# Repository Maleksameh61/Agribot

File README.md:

# The AgriBot rover

> **Stardance reviewers:** the part I'm submitting is the PCB, which is everything in `PCB/` and `production/`. I started AgriBot before I'd even heard of Hack Club, so the chassis, motors and the rest were already underway. They're here so you can see what the board plugs into, but please review the board on its own.

AgriBot tops out at 1.4 km/h, so you can outwalk it, and that's fine, because its job is to drive to a GPS point, stop, push a soil probe into the ground and read moisture, temperature, pH, salinity (EC) and NPK, then go do it again somewhere else.

This repo is the board that runs all of that: three ESP32s, five buck converters, the motor driver links, the stepper for the probe, GPS, a SIM800L and two speakers, on 260 x 150 mm of 2 oz copper.

## How it works

The idea is that nobody drives it most of the time. You give it a list of GPS points and it goes to each one, with two HC-SR04s up front so it doesn't drive into a tree. When it gets there it stops, and a NEMA 17 on a rack and pinion pushes the RS485 soil probe down. Sensors reads the probe and saves the numbers with the GPS position. While it's parked the ESP32-CAM can look at the crops, and if it's too far out for WiFi, the Audio ESP32 texts me through the SIM800L.

You can also drive it from your phone, mostly to get it to the field or out of a ditch. The phone joins the WiFi that Sensors puts up and sends throttle and steering about 20 times a second. Sensors passes that down a UART to Motion, and Motion turns it into left and right speeds for the two Cytron MDD10A drivers. Video goes straight from the ESP32-CAM to your phone over the same WiFi, and two servos aim the camera.

Motion only moves while Sensors keeps talking to it. If 150 ms go by without a command, the motors stop, and that's the entire safety system. Yes, I thought about a real e-stop. At walking pace you can just catch it, and pulling an XT60 kills everything.

Sensors also reads temperature, humidity, pressure, light and an MPU6050, and shows what's going on on a 2.8" Cheap Yellow Display over a 4-pin cable. Audio plays sounds off a microSD through two speakers.

## Why I made it

Salty soil is the big problem on small farms in Egypt, and checking a field means walking it with a probe or sending samples to a lab. I wanted a rover to do the walking. I also wanted every part to come from shops in Cairo. The board and everything that plugs into it, with the JLC order and shipping, comes to about $167. The whole rover is more like $560, and most of that is the four gearmotors (1,200 EGP each at Makers) and the soil probe (3,750 EGP). I didn't see that coming when I picked them.

I took AgriBot to RobotChallenge in Beijing this August and came 4th in FreeStyle Senior. After that I redid the electronics. The plan was three separate boards (Motion, Sensors, Audio) talking over ESP-NOW, and I didn't like the chip that drives the motors depending on radio, so now it's one board with the three ESP32s wired together over UART and Sensors in the middle. Before you ask why there are still three: I counted about 39 GPIOs for everything on here, and a DevKit gives you about 24 you can actually use.

## Pictures

These are renders of the real board file. The boards aren't ordered yet, so no photos.

### PCB layout
Red is top copper, blue is bottom. The big red areas are the 12 V pour and the bottom is almost all ground.

### Front and back

### The three ESP32s
Motion, Sensors and Audio, left to right. Sensors is the only one with its WiFi on.

### Schematic

Full-size PDF: [`production/schematic.pdf`](production/schematic.pdf)

### Wiring
Every cable that leaves the board. The numbers on the board map match the plug names underneath. Wire colours are only suggestions, so go by pin number (pin 1 is the marked end of each plug).

## What's on the board

**Power**
- 2x XT60 inputs, one per 12 V 12 Ah battery pack
- A 20 A fuse on each pack before they join, so a shorted pack can't get fed by the good one
- 2 screw terminals that send 12 V out to the motor drivers
- A 5 A fuse and an MBR4045CT Schottky in front of everything that isn't a motor
- 5x LM2596 buck modules: 5 V for each ESP32, 5 V just for the servos, and 4.0 V for the SIM800L. Every rail has its own LED so you can see when one dies
- Battery voltage sense on Motion and Sensors (100k/22k dividers)
- 12 V pour on top, ground pour on the bottom, 2 oz copper because up to 20 A comes through here

**Motion ESP32**
- Signal connectors for 2x Cytron MDD10A, which run four 5840-31ZY worm gearmotors
- DRV8825 for the NEMA 17 that lowers the soil probe
- 2 servo headers for the camera pan/tilt
- 2 HC-SR04 connectors, with dividers so the 5 V echo doesn't cook the ESP32

**Sensors ESP32**
- AHT20 + BMP280, BH1750 and MPU6050 on one I2C bus
- NEO-6M GPS
- MAX485 module for the RS485 soil probe, plus a 12 V terminal to power the probe
- Cable to the CYD touchscreen
- 8 spare pins on a header for whatever I forgot

**Audio ESP32**
- 2x MAX98357A amps on one shared I2S bus, gain picked with a jumper on each
- microSD
- SIM800L
- 8 more spare pins

## Stuff I'm not sure about yet

A lot of this board is educated guesses, and one guess already nearly went wrong. The first LM2596 footprint was mirrored, so 12 V would have gone straight into the output side of every buck. I only caught it when I swapped in real 3D models and the module didn't line up with its pads. The pads are now 4 mm squares that fit every clone I could find, but I still want to measure one.

- The probe is the part I'm least sure about. A NEMA 17 on a rack and pinion pushes maybe 20 to 50 N, and the rover can't push down harder than it weighs anyway. Soft or tilled soil should be fine. Dry, packed clay, I don't know yet.
- The 5 A fuse covers every buck plus the stepper. My estimate is around 4 A worst case from 12 V, and I haven't measured anything.

## If you build one

- Set every LM2596 to its voltage before it's connected to anything, then hot glue the trimmer. 12 V into a MAX98357A kills it instantly, and the SIM800L wants 4.0 V, not 5.
- Set the DRV8825 current limit before you plug the stepper in.
- Use ceramic 20 A fuses, not glass, and zip tie them down. The clips hold by friction and this thing shakes.
- The camera power terminal has ground on pin 1, the opposite of the other power terminals. It's marked − / + on the board, so look before you screw the wires in.
- Put some kapton tape under each buck module. They sit flat on the board and their bottom pins can scratch through the solder mask.

## AI declaration

Short version: the board is mine, and AI helped me check it.

I drew the schematic, picked every part, and did the placement and routing myself. I used AI kind of like a second pair of eyes. It helped me clear DRC errors and catch problems I missed, and it told me about parts I'd forgotten, mostly passives like decoupling caps, dividers and pull-ups. It also helped me plan which ESP32 pin goes where and what track width to use on the power paths. Some of the custom KiCad symbols and footprints were made by AI, and I checked those against the real modules before using them.

The firmware is where I needed AI the most. It's big, and there were errors I couldn't fix on my own, so AI helped write and debug parts of it, usually one small section at a time. I worked on it for weeks, but you'll only see one commit, because I pushed the wrong versions before and had to upload it all again. There are a lot of comments in the code. I know that can look like AI, but I put them there so you can follow what each part does.

## Files

- `production/` - what you send off to get one made: `gerbers.zip` (Gerbers + drill files), `schematic.pdf` and a copy of the firmware
- `production/printables/` - STEP files for the 3D-printed parts: the four motor mounts and the ESP32-CAM pan/tilt
- `PCB/` - KiCad 10 project (`agribot.kicad_sch`, `agribot.kicad_pcb`, `agribot.kicad_pro`, custom footprints, symbols and 3D models)
- `CAD/agribot-pcb.step` - STEP of the assembled board with every module on it. It's 54 MB, which the GitHub website won't take, so I pushed it with git instead. The module models are real ones (Espressif, KiCad library, Sector7GP, a SIM800L repo, openbikesensor, and the JLCEDA/EasyEDA Official Library for the fuses and the KF128 terminals), credits are in `PCB/libraries/3dmodels/CREDITS.md`
- `CAD/agribot-full-assembly.step` - the whole rover exported from my Fusion file (agribot v15): the plywood chassis with everything mounted on it, including the CYD. 32 MB, so this one went up with git too. Open it if you want to see how it all fits before cutting any wood
- `firmware/` - code for all 5 chips: the Motion, Sensors and Audio ESP32s, the CYD and the ESP32-CAM. How to flash and test it is in `firmware/README.md`
- `BOM.csv` - the bare board: everything on the PCB or plugged into it, from Makers Electronics, Micro Ohm and Free Electronics, with links, USD and EGP prices, shipping, and the JLC quote I got on Nov 3 ($68.80 for 5 boards in 2 oz copper). About $167. The drivers, motors, batteries, probe and chassis aren't in it, since they're not part of the board
- `BOM/AgriBot_Entire_Project_Cost.xlsx` - the whole rover, board plus everything else (motors, drivers, batteries, probe, CYD, camera, chassis, screws). The totals work themselves out, and if you change the EGP rate at the top all the USD numbers change with it

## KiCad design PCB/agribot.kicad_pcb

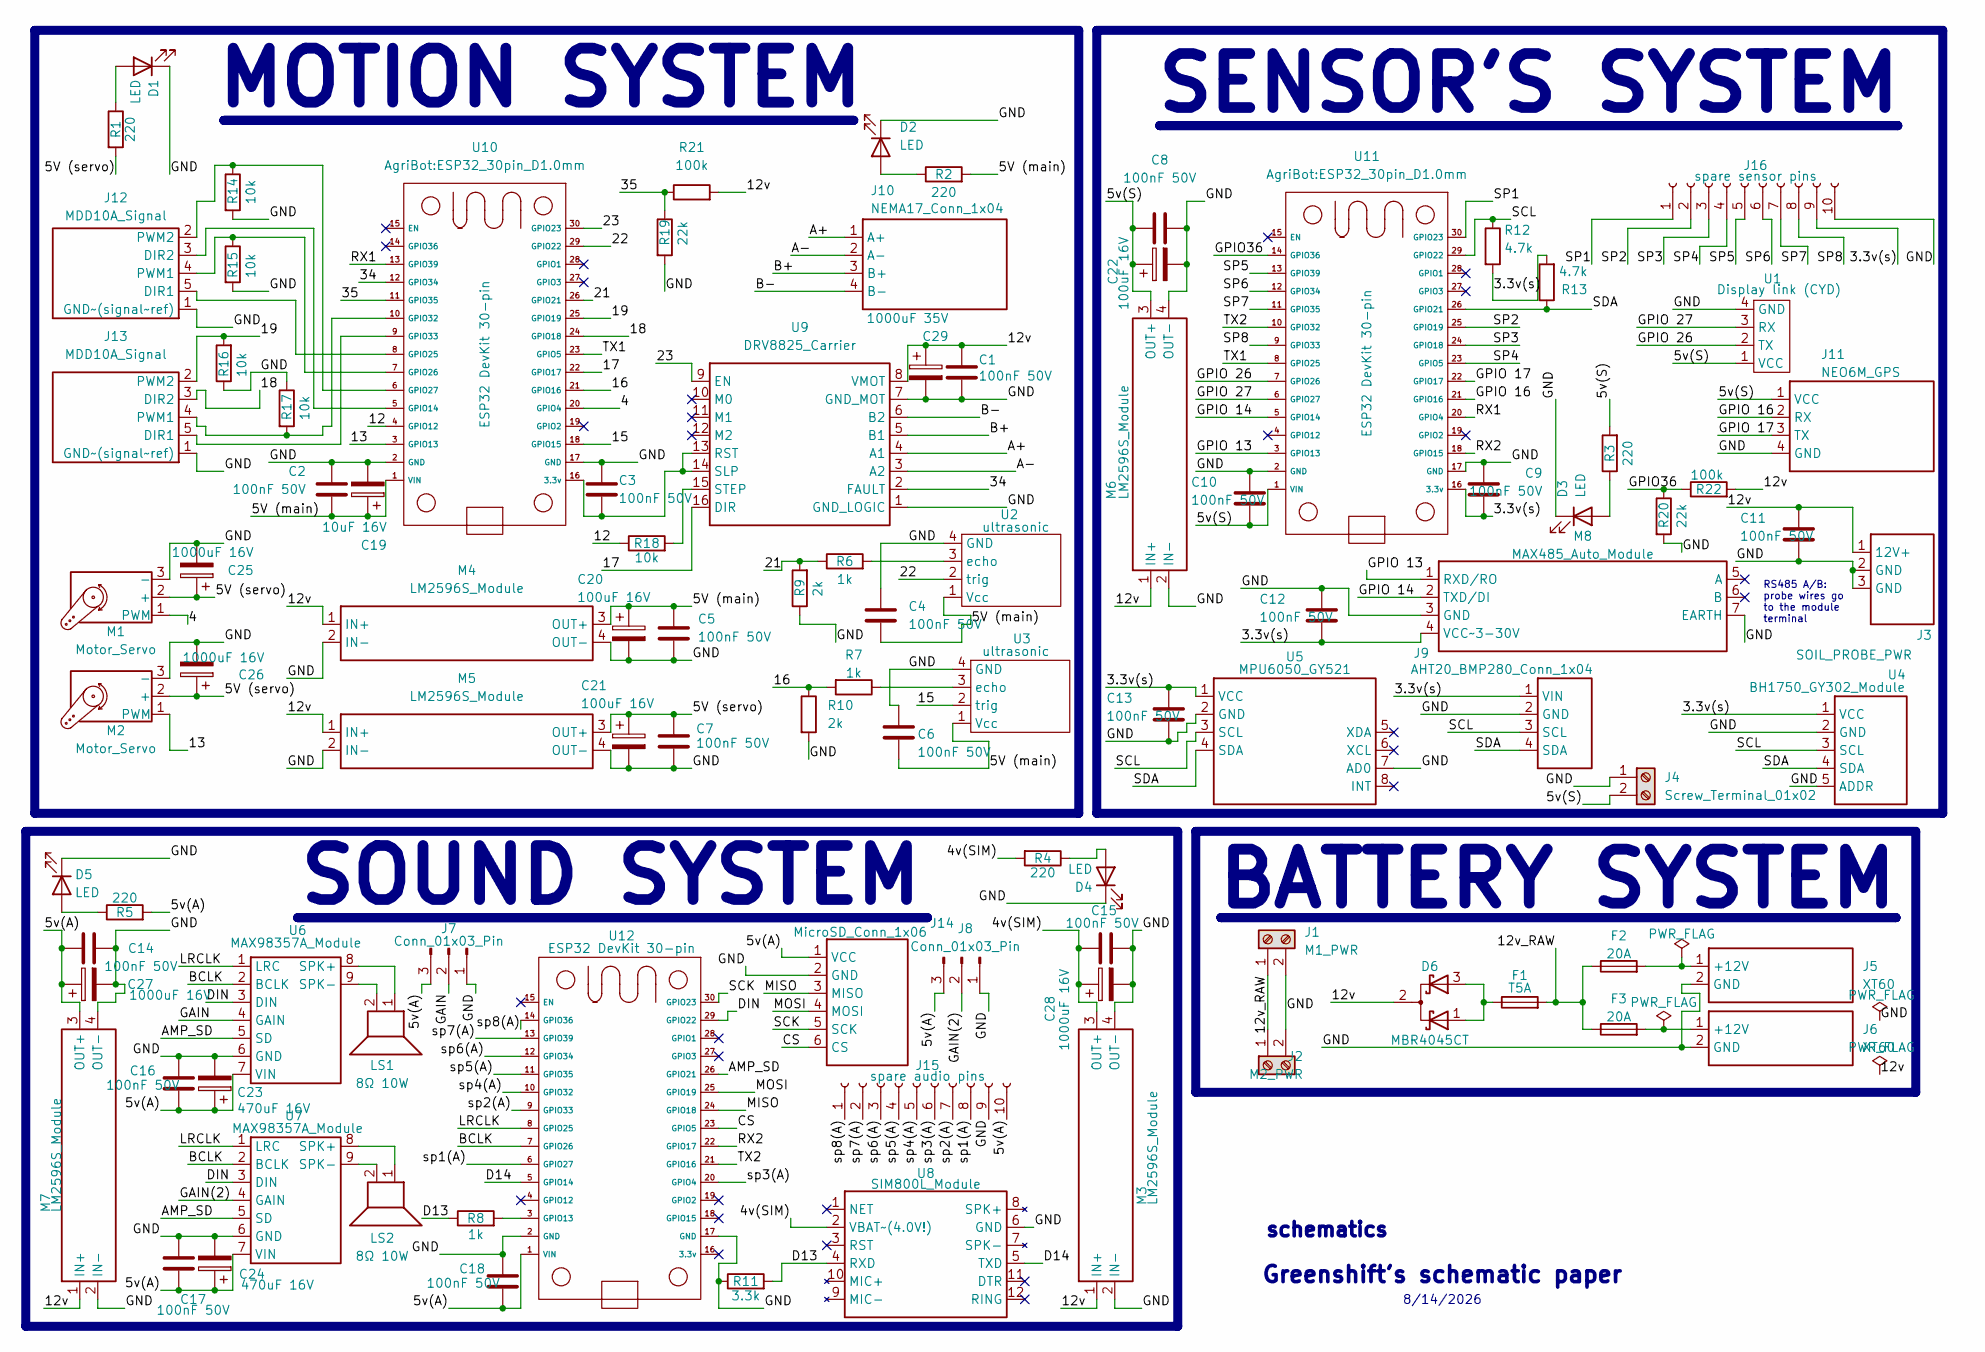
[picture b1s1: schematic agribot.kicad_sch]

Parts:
C1, C2, C3, C4, C5, C6, C7, C8, C9, C10, C11, C12, C13, C14, C15, C16, C17, C18: 100nF 50V; C_Disc_D5.0mm_W2.5mm_P5.00mm
C19: 10uF 16V; CP_Radial_D5.0mm_P2.00mm
C20, C21, C22: 100uF 16V; CP_Radial_D6.3mm_P2.50mm
C23, C24: 470uF 16V; CP_Radial_D10.0mm_P5.00mm
C25, C26, C27, C28: 1000uF 16V; CP_Radial_D10.0mm_P5.00mm
C29: 1000uF 35V; CP_Radial_D13.0mm_P5.00mm
D1, D2, D3, D4, D5: LED; LED_D5.0mm
D6: MBR4045CT; TO-220-3_Vertical
F1: T5A; Fuseholder_Clip-5x20mm_Littelfuse_111_Inline_P20.00x5.00mm_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
F2, F3: 20A; Fuseholder_Clip-5x20mm_Littelfuse_100_Inline_P20.50x4.60mm_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
J1: M1_PWR; KF128-7.5_1x02_P7.50mm_Horizontal
J2: M2_PWR; KF128-7.5_1x02_P7.50mm_Horizontal
J3: SOIL_PROBE_PWR; TerminalBlock_Phoenix_MKDS-1,5-3-5.08_1x03_P5.08mm_Horizont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
J4: Screw_Terminal_01x02; TerminalBlock_Phoenix_MKDS-1,5-2-5.08_1x02_P5.08mm_Horizont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
J5, J6: XT60; AMASS_XT60-M_1x02_P7.20mm_Vertical
J7, J8: Conn_01x03_Pin; PinHeader_1x03_P2.54mm_Vertical
J9: AHT20_BMP280_Conn_1x04; JST_XH_B4B-XH-A_1x04_P2.50mm_Vertical
J10: NEMA17_Conn_1x04; JST_XH_B4B-XH-A_1x04_P2.50mm_Vertical
J11: NEO6M_GPS; JST_XH_B4B-XH-A_1x04_P2.50mm_Vertical
J12, J13: MDD10A_Signal; JST_XH_B5B-XH-A_1x05_P2.50mm_Vertical
J14: MicroSD_Conn_1x06; PinSocket_1x06_P2.54mm_Vertical
J15: spare audio pins; PinSocket_2x05_P2.54mm_Vertical
J16: spare sensor pins; PinSocket_2x05_P2.54mm_Vertical
LS1, LS2: 8Ω 10W
M1, M2: Motor_Servo; PinHeader_1x03_P2.54mm_Vertical
M3, M4, M5, M6, M7: LM2596S_Module; LM2596S_Module_FlatMount_SMD
M8: MAX485_Auto_Module; JST_XH_B4B-XH-A_1x04_P2.50mm_Vertical
R1, R2, R3, R4, R5: 220; R_Axial_DIN0207_L6.3mm_D2.5mm_P10.16mm_Horizontal
R6, R7, R8: 1k; R_Axial_DIN0207_L6.3mm_D2.5mm_P10.16mm_Horizontal
R9, R10: 2k; R_Axial_DIN0207_L6.3mm_D2.5mm_P10.16mm_Horizontal
R11: 3.3k; R_Axial_DIN0207_L6.3mm_D2.5mm_P10.16mm_Horizontal
R12, R13: 4.7k; R_Axial_DIN0207_L6.3mm_D2.5mm_P10.16mm_Horizontal
R14, R15, R16, R17, R18: 10k; R_Axial_DIN0207_L6.3mm_D2.5mm_P10.16mm_Horizontal
R19, R20: 22k; R_Axial_DIN0207_L6.3mm_D2.5mm_P10.16mm_Horizontal
R21, R22: 100k; R_Axial_DIN0207_L6.3mm_D2.5mm_P10.16mm_Horizontal
U1: Display link (CYD); JST_XH_B4B-XH-A_1x04_P2.50mm_Vertical
U2, U3: ultrasonic; JST_XH_B4B-XH-A_1x04_P2.50mm_Vertical
U4: BH1750_GY302_Module; JST_XH_B5B-XH-A_1x05_P2.50mm_Vertical
U5: MPU6050_GY521; PinSocket_1x08_P2.54mm_Vertical
U6, U7: MAX98357A_Module; PinSocket_1x07_P2.54mm_Vertical
U8: SIM800L_Module
U9: DRV8825_Carrier; Pololu_Breakout-16_15.2x20.3mm_D1.0mm
U10, U11, U12: ESP32 DevKit 30-pin; ESP32_30pin_D1.0mm

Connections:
/3.3v(s): C9.2, C12.2, C13.1, J9.1 (VIN), J16.9, M8.4 (VCC~3-30V), R12.2, R13.2, U4.1 (VCC), U5.1 (VCC), U11.16 (3.3v)
/4: M1.1 (PWM), U10.20 (GPIO4)
/4v(SIM): C15.2, C28.1, M3.3 (OUT+), R4.2, U8.2 (VBAT~(4.0V!))
/5V (main): C2.2, C4.2, C5.1, C6.2, C19.1, C20.1, M4.3 (OUT+), R2.2, U2.1 (Vcc), U3.1 (Vcc), U10.1 (VIN)
/5V (servo): C7.1, C21.1, C25.1, C26.1, M1.2 (+), M2.2 (+), M5.3 (OUT+), R1.2
/5v(A): C14.2, C16.1, C17.1, C18.2, C23.1, C24.1, C27.1, J7.3, J8.3, J14.1 (VCC), J15.10, M7.3 (OUT+), R5.2, U6.7 (VIN), U7.7 (VIN), U12.1 (VIN)
/5v(S): C8.1, C10.2, C22.1, J4.2, J11.1 (VCC), M6.3 (OUT+), R3.2, U1.1 (VCC), U11.1 (VIN)
/12: R18.1, U10.4 (GPIO12)
/12v: C1.1, C11.1, C29.1, D6.2 (K), J3.1 (12V+), M3.1 (IN+), M4.1 (IN+), M5.1 (IN+), M6.1 (IN+), M7.1 (IN+), R21.2, R22.2, U9.8 (VMOT)
/12v_RAW: F1.2, F2.1, F3.1, J1.1, J2.1
/13: M2.1 (PWM), U10.3 (GPIO13)
/15: U3.2 (trig), U10.18 (GPIO15)
/16: R7.2, R10.1, U10.21 (GPIO16)
/17: U9.16 (DIR), U10.22 (GPIO17)
/18: J13.3 (DIR2), U10.24 (GPIO18)
/19: J13.2 (PWM2), R16.2, U10.25 (GPIO19)
/21: R6.1, R9.2, U10.26 (GPIO21)
/22: U2.2 (trig), U10.29 (GPIO22)
/23: U9.9 (EN), U10.30 (GPIO23)
/34: U9.2 (FAULT), U10.12 (GPIO34)
/35: R19.1, R21.1, U10.11 (GPIO35)
/A+: J10.1 (A+), U9.4 (A1)
/A-: J10.2 (A-), U9.3 (A2)
/AMP_SD: U6.5 (SD), U7.5 (SD), U12.26 (GPIO21)
/B+: J10.3 (B+), U9.5 (B1)
/B-: J10.4 (B-), U9.6 (B2)
/BCLK: U6.2 (BCLK), U7.2 (BCLK), U12.7 (GPIO26)
/CS: J14.6 (CS), U12.23 (GPIO5)
/D13: R8.1, R11.2, U8.4 (RXD)
/D14: U8.5 (TXD), U12.5 (GPIO14)
/DIN: U6.3 (DIN), U7.3 (DIN), U12.29 (GPIO22)
/GAIN: J7.2, U6.4 (GAIN)
/GAIN(2): J8.2, U7.4 (GAIN)
/GND: C1.2, C2.1, C3.1, C4.1, C5.2, C6.1, C7.2, C8.2, C9.1, C10.1, C11.2, C12.1, C13.2, C14.1, C15.1, C16.2, C17.2, C18.1, C19.2, C20.2, C21.2, C22.2, C23.2, C24.2, C25.2, C26.2, C27.2, C28.2, C29.2, D1.1 (K), D2.1 (K), D3.1 (K), D4.1 (K), D5.1 (K), J1.2, J2.2, J3.2 (GND), J3.3 (GND), J4.1, J5.2 (GND), J6.2 (GND), J7.1, J8.1, J9.2 (GND), J11.4 (GND), J12.1 (GND~(signal~ref)), J13.1 (GND~(signal~ref)), J14.2 (GND), J15.9, J16.10, M1.3 (-), M2.3 (-), M3.2 (IN-), M3.4 (OUT-), M4.2 (IN-), M4.4 (OUT-), M5.2 (IN-), M5.4 (OUT-), M6.2 (IN-), M6.4 (OUT-), M7.2 (IN-), M7.4 (OUT-), M8.3 (GND), M8.7 (EARTH), R9.1, R10.2, R11.1, R14.2, R15.2, R16.1, R17.1, R19.2, R20.2, U1.4 (GND), U2.4 (GND), U3.4 (GND), U4.2 (GND), U4.5 (ADDR), U5.2 (GND), U5.7 (AD0), U6.6 (GND), U7.6 (GND), U8.6 (GND), U9.1 (GND_LOGIC), U9.7 (GND_MOT), U10.2 (GND), U10.17 (GND), U11.2 (GND), U11.17 (GND), U12.2 (GND), U12.17 (GND)
/GPIO36: R20.1, R22.1, U11.14 (GPIO36)
/GPIO 13: M8.1 (RXD/RO), U11.3 (GPIO13)
/GPIO 14: M8.2 (TXD/DI), U11.5 (GPIO14)
/GPIO 16: J11.2 (RX), U11.21 (GPIO16)
/GPIO 17: J11.3 (TX), U11.22 (GPIO17)
/GPIO 26: U1.2 (TX), U11.7 (GPIO26)
/GPIO 27: U1.3 (RX), U11.6 (GPIO27)
/LRCLK: U6.1 (LRC), U7.1 (LRC), U12.8 (GPIO25)
/MISO: J14.3 (MISO), U12.24 (GPIO18)
/MOSI: J14.4 (MOSI), U12.25 (GPIO19)
/RX1: U10.13 (GPIO39), U11.20 (GPIO4)
/RX2: U11.18 (GPIO15), U12.22 (GPIO17)
/SCK: J14.5 (SCK), U12.30 (GPIO23)
/SCL: J9.3 (SCL), R12.1, U4.3 (SCL), U5.3 (SCL), U11.29 (GPIO22)
/SDA: J9.4 (SDA), R13.1, U4.4 (SDA), U5.4 (SDA), U11.26 (GPIO21)
/SP1: J16.1, U11.30 (GPIO23)
/SP2: J16.2, U11.25 (GPIO19)
/SP3: J16.3, U11.24 (GPIO18)
/SP4: J16.4, U11.23 (GPIO5)
/SP5: J16.5, U11.13 (GPIO39)
/SP6: J16.6, U11.12 (GPIO34)
/SP7: J16.7, U11.11 (GPIO35)
/SP8: J16.8, U11.9 (GPIO33)
/TX1: U10.23 (GPIO5), U11.8 (GPIO25)
/TX2: U11.10 (GPIO32), U12.21 (GPIO16)
/sp1(A): J15.8, U12.6 (GPIO27)
/sp2(A): J15.7, U12.9 (GPIO33)
/sp3(A): J15.6, U12.20 (GPIO4)
/sp4(A): J15.5, U12.10 (GPIO32)
/sp5(A): J15.4, U12.11 (GPIO35)
/sp6(A): J15.3, U12.12 (GPIO34)
/sp7(A): J15.2, U12.13 (GPIO39)
/sp8(A): J15.1, U12.14 (GPIO36)
unnamed: D1.2 (A), R1.1
unnamed: D2.2 (A), R2.1
unnamed: D3.2 (A), R3.1
unnamed: D4.2 (A), R4.1
unnamed: D5.2 (A), R5.1
unnamed: D6.1 (A), D6.3 (A), F1.1
unnamed: F2.2, J5.1 (+12V)
unnamed: F3.2, J6.1 (+12V)
unnamed: J12.5 (DIR1), U10.8 (GPIO25)
unnamed: J12.3 (DIR2), U10.5 (GPIO14)
unnamed: J12.4 (PWM1), R15.1, U10.7 (GPIO26)
unnamed: J12.2 (PWM2), R14.1, U10.6 (GPIO27)
unnamed: J13.5 (DIR1), U10.9 (GPIO33)
unnamed: J13.4 (PWM1), R17.2, U10.10 (GPIO32)
unnamed: LS1.1, U6.8 (SPK+)
unnamed: LS1.2, U6.9 (SPK-)
unnamed: LS2.1, U7.8 (SPK+)
unnamed: LS2.2, U7.9 (SPK-)
unnamed: R6.2, U2.3 (echo)
unnamed: R7.1, U3.3 (echo)
unnamed: R18.2, U9.15 (STEP)
unnamed: C3.2, U9.13 (RST), U9.14 (SLP), U10.16 (3.3v)
unnamed: R8.2, U12.3 (GPIO13)

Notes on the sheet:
BATTERY SYSTEM
Greenshift's schematic paper
schematics
SOUND SYSTEM
RS485 A/B: probe wires go to the module terminal
MOTION SYSTEM
8/14/2026
SENSOR'S SYSTEM

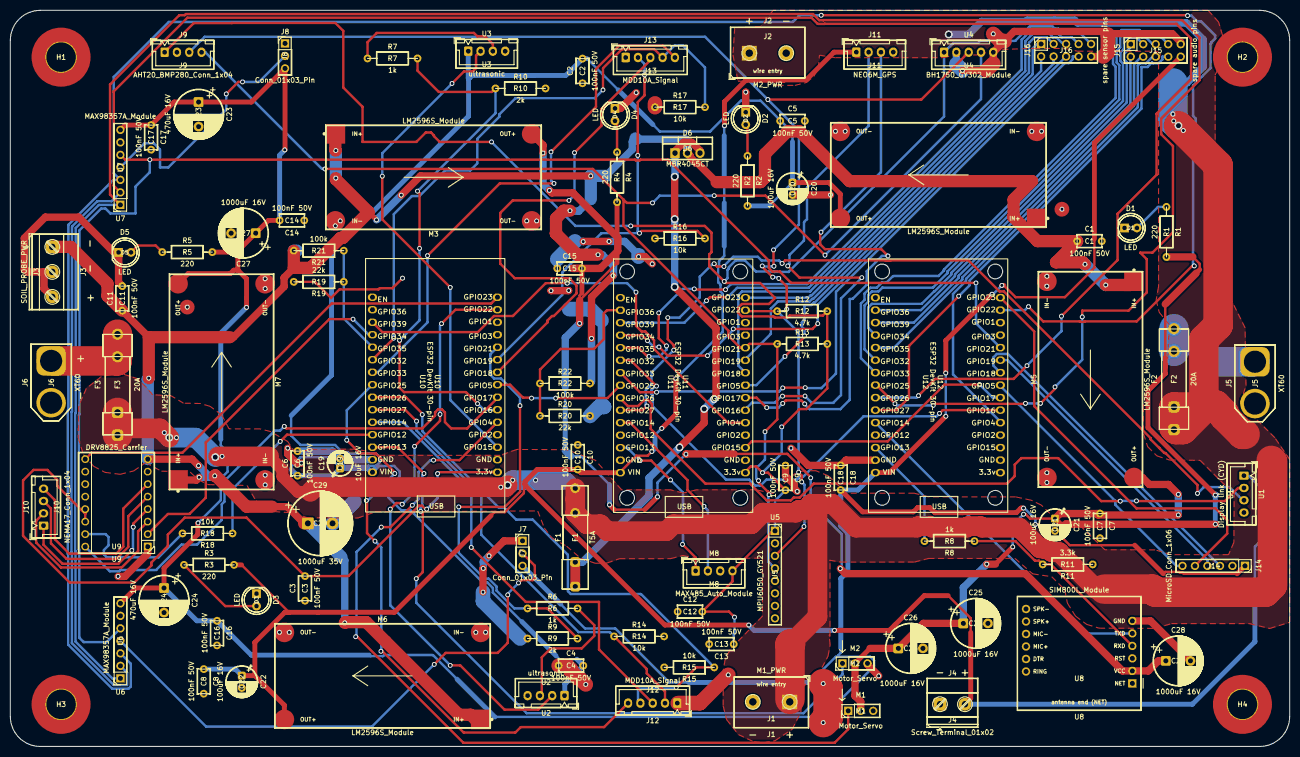
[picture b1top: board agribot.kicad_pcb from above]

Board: 2 copper layers, 260.0 x 149.6 mm, 100 parts (0 on the bottom side), 86 nets.

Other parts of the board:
H1, H2, H3, H4: MountingHole_6mm_Pad_TopBottom

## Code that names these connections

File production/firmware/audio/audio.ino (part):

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  sc.clk_cfg = I2S_STD_CLK_DEFAULT_CONFIG(rate);
  sc.slot_cfg = I2S_STD_PHILIPS_SLOT_DEFAULT_CONFIG(I2S_DATA_BIT_WIDTH_16BIT, I2S_SLOT_MODE_STEREO);
  sc.gpio_cfg.mclk = I2S_GPIO_UNUSED;
  sc.gpio_cfg.bclk = (gpio_num_t)I2S_BCLK;
  sc.gpio_cfg.ws   = (gpio_num_t)I2S_LRCLK;
  sc.gpio_cfg.dout = (gpio_num_t)I2S_DOUT;
  sc.gpio_cfg.din  = I2S_GPIO_UNUSED;
  ESP_ERROR_CHECK(i2s_channel_init_std_mode(i2sTx, &sc));
  ESP_ERROR_CHECK(i2s_channel_enable(i2sTx));
  currentRate = rate;
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}

void setup() {
  pinMode(AMP_SD, OUTPUT); digitalWrite(AMP_SD, LOW);   // amps off until audio starts
  Serial.begin(115200);
  Serial.println("\nAgriBot AUDIO");

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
